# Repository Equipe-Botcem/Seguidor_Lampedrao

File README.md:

# Seguidor_Alpha

Código utilizado para controle e envio de comandos do robô seguidor de linha da equipe de competição BOTCEM UFSC.

## Índice

1. [Guia de Instalação e Execução](#Guia-de-Instalação-e-Execução)
2. [Pré-requisitos](#Pré-requisitos)
3. [Autoria e Contribuições](#Autoria-e-Contribuições)
4. [Fontes](#Fontes)
5. [Classes e Funções](#Classes-e-Funções)
    1. [Classe `Motor`](#Classe-Motor)
    2. [Classe `Driver`](#Classe-Driver)
    3. [Classe `Controlador`](#Classe-Controlador)
    4. [Classe `Seguidor`](#Classe-Seguidor)

## Guia de Instalação e Execução:

1. Extrair o arquivo zip.
2. Abrir a pasta `esp32_code` com a extensão PlatformIO do VScode.
3. Compilar o arquivo e transferi-lo para o ESP32.
4. Baixar o aplicativo Line-follower.apk.

## Pré-requisitos:

- Microcontrolador: esp32dev
- Sistema operacional: Linux 20.04
- IDE: Visual Studio Code
- Framework: Arduino

## Autoria e Contribuições:

Esse projeto é de autoria da equipe BOTCEM UFSC.

## Fontes:

Stack Overflow, c2022. Disponível em: <stackoverflow.com>. Acesso em: 18 de dezembro de 2022.

## Classes e Funções

Este projeto inclui várias classes e funções para controlar o robô. As classes incluem `Motor`, `Driver`, `Controlador` e `Seguidor`, cada uma responsável por um aspecto específico do controle do robô. As funções dentro dessas classes permitem controlar os motores, ler os sensores, calcular a saída do controlador PID, e mais.

Para obter uma descrição detalhada de cada classe e função, consulte a documentação do código-fonte. Aqui estão alguns destaques:

- `Motor`: Esta classe controla o motor de cada lado do robô.
- `Driver`: Esta classe controla os dois motores do robô.
- `Controlador`: Esta classe implementa um controlador PID (Proporcional, Integral, Derivativo).
- `Seguidor`: Esta classe é o principal controlador do robô seguidor de linha.

### Classe `Motor`

Essa classe controla o motor de cada lado do robô.

- `Motor(unsigned char PWM_1, unsigned char PWM_2, unsigned char EN, unsigned char OCM)`: Construtor da classe. Inicializa um motor com base nos pinos PWM, de habilitação (EN) e OCM.

- `void Init()`: Define os modos dos pinos como OUTPUT.

- `void Enable_drive()`: Habilita a unidade de motor acionando o pino EN.

- `void Disable_drive()`: Desabilita a unidade de motor e para o motor.

- `void Set_speed(int speed)`: Define a velocidade do motor. A velocidade pode ser positiva ou negativa, indicando a direção do motor.

### Classe `Driver`

Essa classe controla os dois motores do robô.

- `Driver(unsigned char *pins_dir, unsigned char *pins_esq)`: Construtor da classe. Inicializa os motores esquerdo e direito com base nos pinos fornecidos.

- `void Init()`: Inicializa os motores.

- `void setVB(int vb)`: Define a velocidade base dos motores.

- `void setMotors(int speed_esq, int speed_dir)`: Define a velocidade dos motores esquerdo e direito.

- `void Enable_motors_drives()`: Habilita os dois motores.

- `void Disable_motors_drives()`: Desabilita os dois motores.

- `void Break()`: Para os motores.

- `void Set_speedRot(int rot)`: Define a velocidade rotacional dos motores.

- `void teste()`: Uma função de teste que move os motores para frente e para trás.

### Classe `Controlador`

Essa classe implementa um controlador PID (Proporcional, Integral, Derivativo).

- `Controlador()`: Construtor da classe.

- `void setKp(float kp)`: Define o coeficiente proporcional do PID.

- `void setKd(float kd)`: Define o coeficiente derivativo do PID.

- `void setKi(float ki)`: Define o coeficiente integral do PID.

- `void setControlador(float kp, float kd, float ki)`: Define todos os coeficientes do PID.

- `float calcPID(float erro)`: Calcula a saída do PID com base no erro fornecido.

- `float getAmostragem()`: Retorna o tempo de amostragem do PID.

- `void resetConditions()`: Reseta as condições do PID.

- `void teste(float erro)`: Uma função de teste que imprime a saída do PID.

### Classe `Seguidor`

Essa classe é o principal controlador do robô seguidor de linha.

- `Seguidor()`: Construtor da classe.

- `void Config_...()`: Um conjunto de funções que configuram os pinos, sensores e motores do robô.

- `void initBluetooth()`: Inicializa a conexão Bluetooth.

- `void Init()`: Inicializa todos os componentes do robô.

- `void set_handler()`: Manipula os comandos recebidos pelo Bluetooth.

- `void calibration()`: Calibra os sensores de linha.

- `void controle()`: Controla os motores com base nos sensores de linha.

- `bool IsOut()`: Verifica se o robô está fora da linha.

- `void mapeamento()`: Mapeia o caminho do robô.

- `void Run()`: Inicia o robô.

- `void Stop()`: Para o robô.

- `void Behavior()`: Controla o comportamento do robô com base nos comandos recebidos pelo Bluetooth.

- `void comunica_serial()`: Lê comandos do Bluetooth.

- `void stopRoutine()`: Rotina para parar o robô.

- `bool CheckLateralDir()`, `bool CheckLateralEsq()`: Verifica se o robô chegou a um cruzamento à direita ou à esquerda.

- `bool isStart()`: Verifica se o robô está em movimento.

- `void bateryCheck()`: Verifica o nível da bateria.

- `void CheckLed()`, `void LigaLed()`, `void DesligaLed()`, `void PiscaLed(int num_piscadas)`: Funções para controlar os LEDs do robô.

- `void teste()`, `void TesteSensoresLat()`: Funções de teste para o robô.

### Diagrama de classes

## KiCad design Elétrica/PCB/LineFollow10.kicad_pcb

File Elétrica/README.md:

# Documentação do Projeto Eletrônico do Seguidor de Linha Alpha

## 1. Projeto Elétrico

O projeto elétrico tem seu funcionamento separado em três parte: potência (alimentação) e controle.

### 1.1. Potência

O circuito de potência é composto pelos seguintes elementos:

- Bateria: LiPo 7,4V 2S 300mAh;
- Conversor de tensão Step Up: XL6009;
- Regulador de Tensão 5V: LM7805;
- Regulador de Tensão 3.3V: LM1117;
- Capacitores de Filtro: 0.22uF, 0.1uF e 10uF.
- Diodo;
- Switchs.

### 1.2. Controle

O circuito de controle é composto pelos seguintes elementos:

- Shield ESP32;
- Drivers IC: TB9051FTG Single Brushed;
- Encoders;
- Sensores de Refletância: QRE1117;
- Resistores: 47Kohns e 47ohns.

## 2. Projeto da PCB

O projeto da PCB foi desenvolvido no software KiCAD.
As dimensões da placa são: 119mm X 151mm X 1.6mm (Comprimento X Largura X Altura).
A placa é composta por duas camadas de trilhas, inferior e superior.

## 3. Medições

### 3.1. Corrente Consumida

Realizando a medição do Seguidor de Linha por uma fonte de tensão, pode-se obter as seguintes medidas de consumo:

- Ligado: 300mA;
- Velocidade Baixa: 600mA;
- Velocidade Alta: 1.5A. 

## 4. Melhorias

- Desenvolvimento de uma placa totalmente integrada.

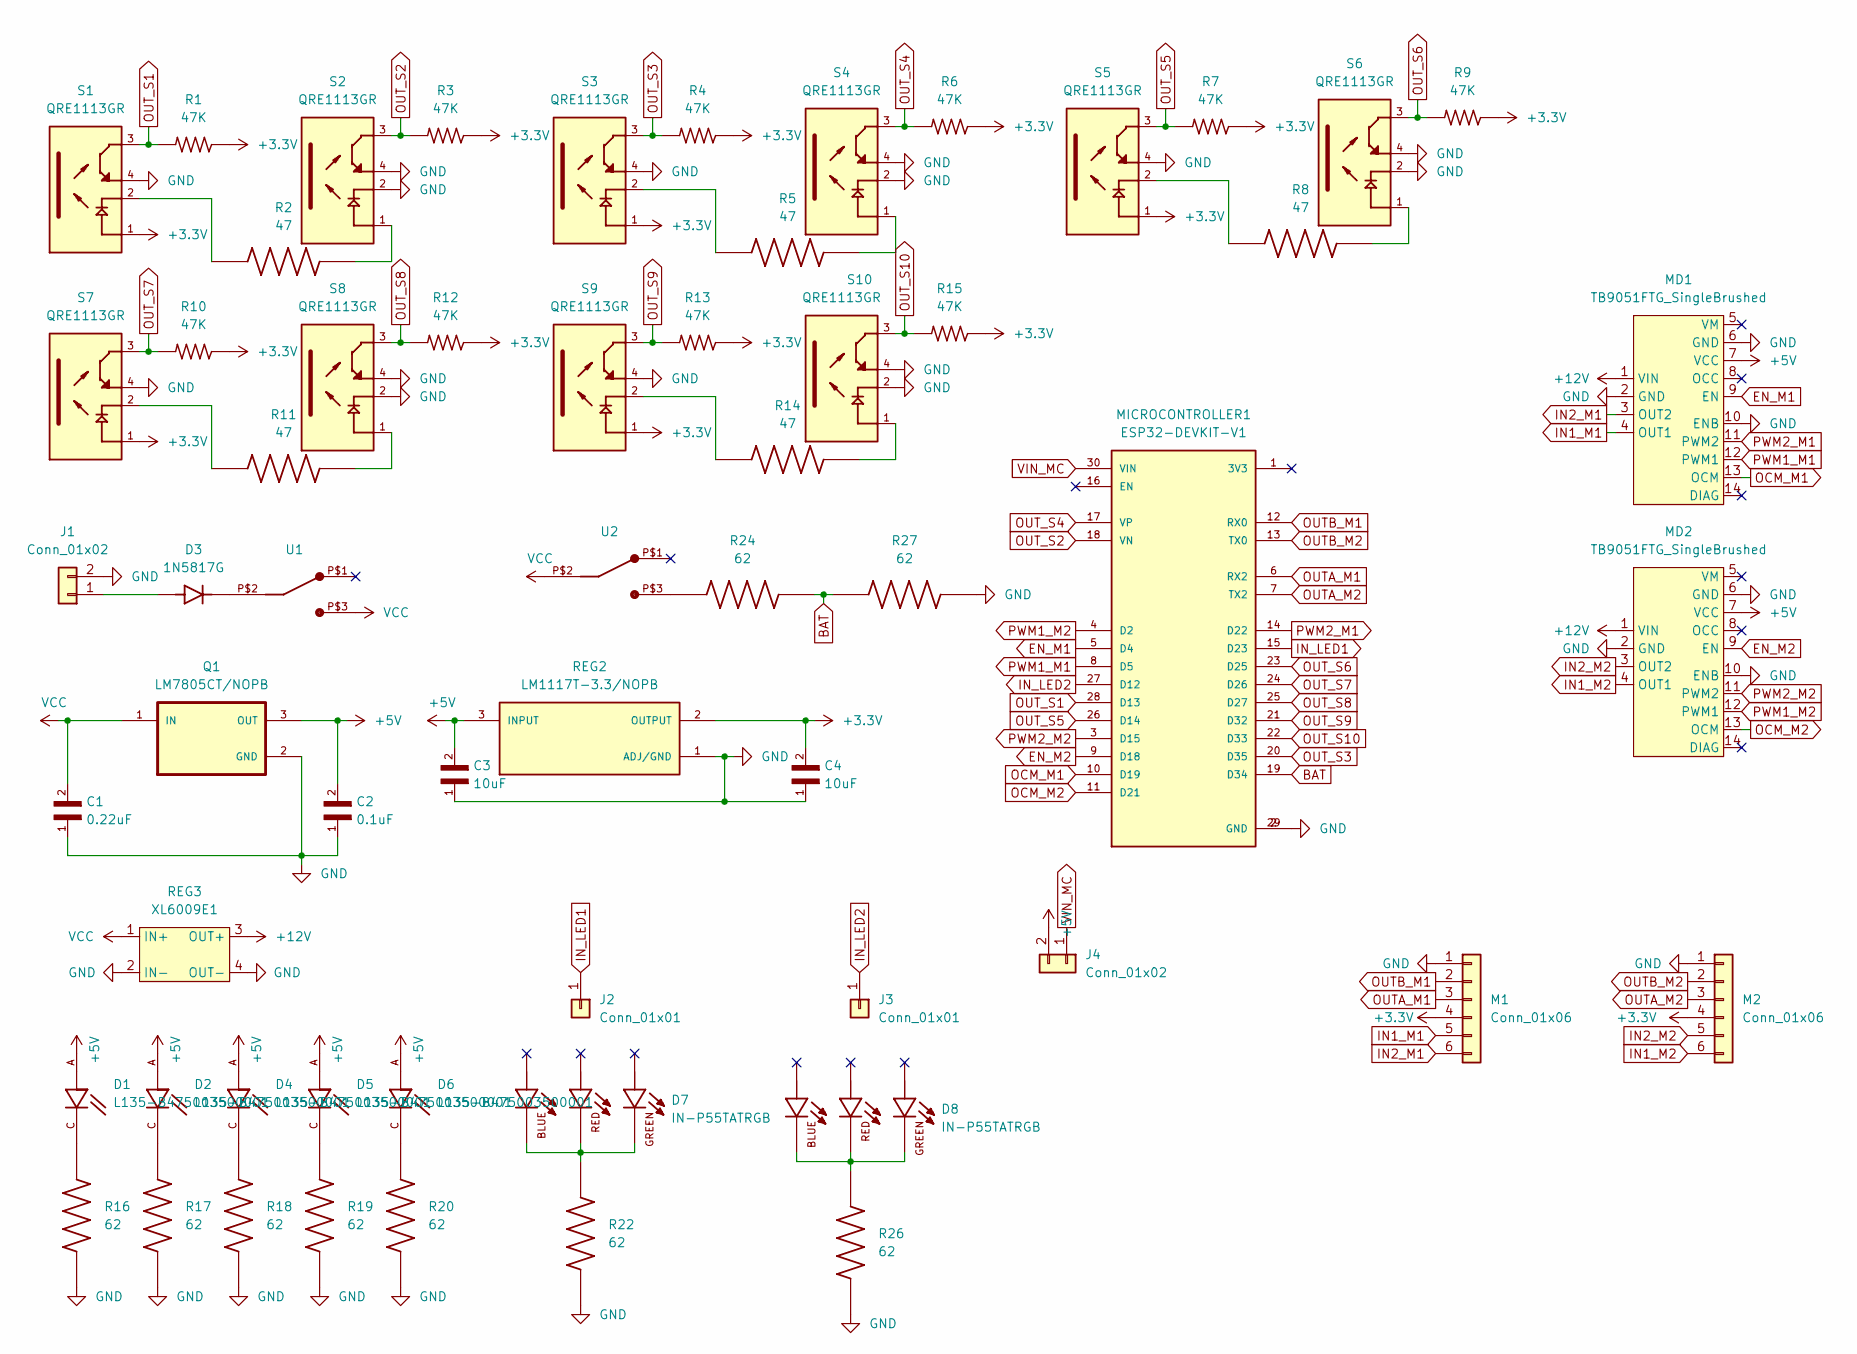
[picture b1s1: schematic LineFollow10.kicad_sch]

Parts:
C1: 0.22uF; CAPRB250W50L550T350H600; PARTREV 20200318
C2: 0.1uF; CAPRB500W50L450T300H550; PARTREV 20200310
C3, C4: 10uF; CAPRB500W50L450T300H550; PARTREV 20200310
D1, D2, D4, D5, D6: L135-B475003500001; LED_L135-B475003500001
D3: 1N5817G; DIOAD1036W78L470D235; PARTREV P2104
D7, D8: IN-P55TATRGB; LED_IN-P55TATRGB; PARTREV 1.0
J1: Conn_01x02; PinSocket_1x02_P2.54mm_Vertical
J2: Conn_01x01; SolderWire-0.1sqmm_1x01_D0.4mm_OD1mm
J3: Conn_01x01
J4: Conn_01x02
M1, M2: Conn_01x06; PinSocket_1x06_P2.54mm_Vertical
MD1, MD2: TB9051FTG_SingleBrushed
MICROCONTROLLER1: ESP32-DEVKIT-V1; MODULE_ESP32_DEVKIT_V1; PARTREV N/A
Q1: LM7805CT/NOPB; TO254P1054X470X2600-3; PARTREV LTR
R1, R3, R4, R6, R7, R9, R10, R12, R13, R15: 47K; RESAD640W45L370D200
R2, R5, R8, R11, R14: 47; RESAD716W44L360D186; PARTREV 11/16/2017
R16, R17, R18, R19, R20, R22, R24, R26, R27: 62; RESAD1100W55L680D260; PARTREV 201304
REG2: LM1117T-3.3/NOPB; TO254P1054X470X1955-3; PARTREV O
REG3: XL6009E1
S1, S2, S3, S4, S5, S6, S7, S8, S9, S10: QRE1113GR; SOIC180P460X187-4N; PARTREV 5
U1, U2: 0S102011MS2QN1

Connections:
+3.3V: C4.2, M1.4, M2.4, R1.1, R3.1, R4.1, R6.1, R7.1, R9.1, R10.1, R12.1, R13.1, R15.1, REG2.2 (OUTPUT), S1.1, S3.1, S5.1, S7.1, S9.1
+5V: C2.2, C3.2, D1.A, D2.A, D4.A, D5.A, D6.A, J4.2, MD1.7 (VCC), MD2.7 (VCC), Q1.3 (OUT), REG2.3 (INPUT)
+12V: MD1.1 (VIN), MD2.1 (VIN), REG3.3 (OUT+)
BAT: MICROCONTROLLER1.19 (D34), R24.1, R27.2
EN_M1: MD1.9 (EN), MICROCONTROLLER1.5 (D4)
EN_M2: MD2.9 (EN), MICROCONTROLLER1.9 (D18)
GND: C1.1, C2.1, C3.1, C4.1, J1.2, M1.1, M2.1, MD1.2 (GND), MD1.6 (GND), MD1.10 (ENB), MD2.2 (GND), MD2.6 (GND), MD2.10 (ENB), MICROCONTROLLER1.2 (GND), MICROCONTROLLER1.29 (GND), Q1.2 (GND), R16.1, R17.1, R18.1, R19.1, R20.1, R22.1, R26.1, R27.1, REG2.1 (ADJ/GND), REG3.2 (IN-), REG3.4 (OUT-), S1.4, S2.2, S2.4, S3.4, S4.2, S4.4, S5.4, S6.2, S6.4, S7.4, S8.2, S8.4, S9.4, S10.2, S10.4
IN1_M1: M1.5, MD1.4 (OUT1)
IN1_M2: M2.6, MD2.4 (OUT1)
IN2_M1: M1.6, MD1.3 (OUT2)
IN2_M2: M2.5, MD2.3 (OUT2)
IN_LED1: J2.1, MICROCONTROLLER1.15 (D23)
IN_LED2: J3.1, MICROCONTROLLER1.27 (D12)
unnamed: D1.C, R16.2
unnamed: D2.C, R17.2
unnamed: D3.A, J1.1
unnamed: D3.C, U1.P$2
unnamed: D4.C, R18.2
unnamed: D5.C, R19.2
unnamed: D6.C, R20.2
unnamed: D7.1, D7.2, D7.3, R22.2
unnamed: D8.1, D8.2, D8.3, R26.2
unnamed: R2.1, S1.2
unnamed: R2.2, S2.1
unnamed: R5.1, S3.2
unnamed: R5.2, S4.1
unnamed: R8.1, S5.2
unnamed: R8.2, S6.1
unnamed: R11.1, S7.2
unnamed: R11.2, S8.1
unnamed: R14.1, S9.2
unnamed: R14.2, S10.1
unnamed: R24.2, U2.P$3
OCM_M1: MD1.13 (OCM), MICROCONTROLLER1.10 (D19)
OCM_M2: MD2.13 (OCM), MICROCONTROLLER1.11 (D21)
OUTA_M1: M1.3, MICROCONTROLLER1.6 (RX2)
OUTA_M2: M2.3, MICROCONTROLLER1.7 (TX2)
OUTB_M1: M1.2, MICROCONTROLLER1.12 (RX0)
OUTB_M2: M2.2, MICROCONTROLLER1.13 (TX0)
OUT_S1: MICROCONTROLLER1.28 (D13), R1.2, S1.3
OUT_S2: MICROCONTROLLER1.18 (VN), R3.2, S2.3
OUT_S3: MICROCONTROLLER1.20 (D35), R4.2, S3.3
OUT_S4: MICROCONTROLLER1.17 (VP), R6.2, S4.3
OUT_S5: MICROCONTROLLER1.26 (D14), R7.2, S5.3
OUT_S6: MICROCONTROLLER1.23 (D25), R9.2, S6.3
OUT_S7: MICROCONTROLLER1.24 (D26), R10.2, S7.3
OUT_S8: MICROCONTROLLER1.25 (D27), R12.2, S8.3
OUT_S9: MICROCONTROLLER1.21 (D32), R13.2, S9.3
OUT_S10: MICROCONTROLLER1.22 (D33), R15.2, S10.3
PWM1_M1: MD1.12 (PWM1), MICROCONTROLLER1.8 (D5)
PWM1_M2: MD2.12 (PWM1), MICROCONTROLLER1.4 (D2)
PWM2_M1: MD1.11 (PWM2), MICROCONTROLLER1.14 (D22)
PWM2_M2: MD2.11 (PWM2), MICROCONTROLLER1.3 (D15)
VCC: C1.2, Q1.1 (IN), REG3.1 (IN+), U1.P$3, U2.P$2
VIN_MC: J4.1, MICROCONTROLLER1.30 (VIN)

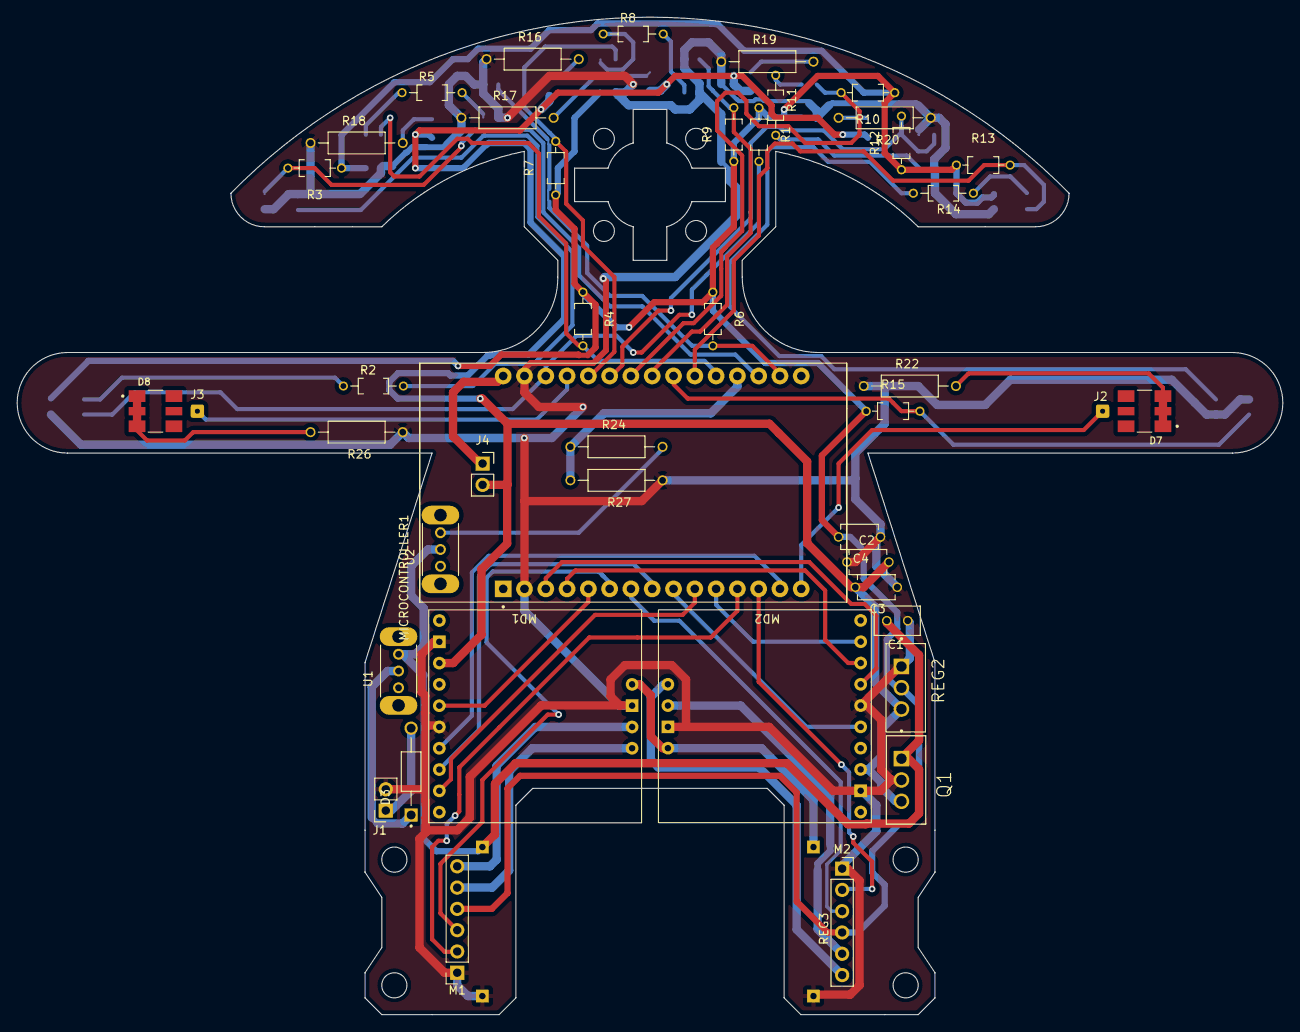
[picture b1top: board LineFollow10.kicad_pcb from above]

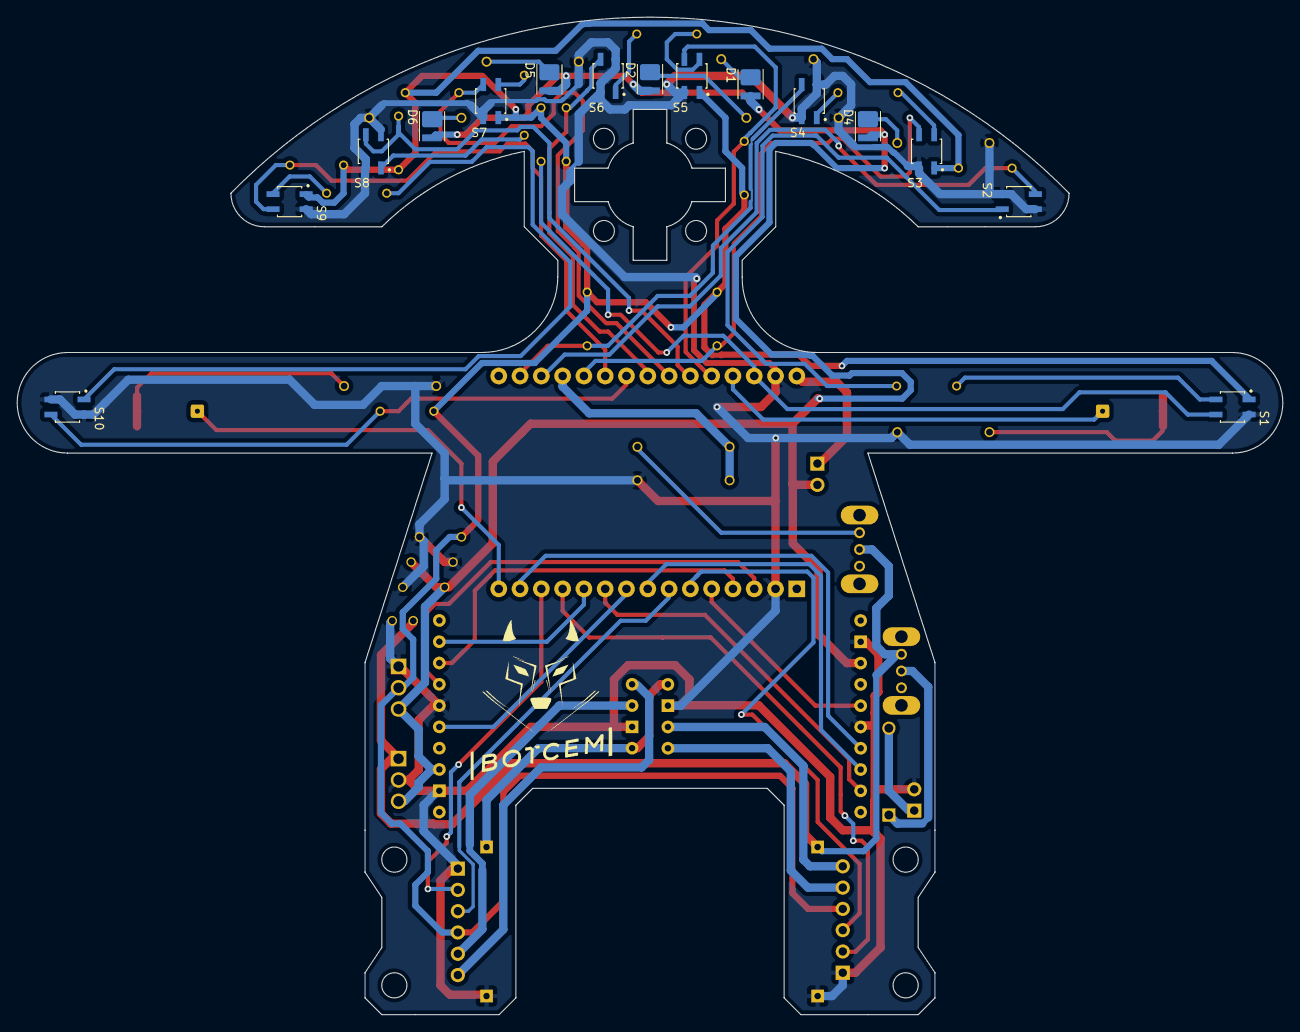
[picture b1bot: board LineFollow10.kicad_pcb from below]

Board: 2 copper layers, 151.0 x 119.0 mm, 64 parts (16 on the bottom side), 55 nets.

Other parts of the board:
G: LOGO; BOTCEMLOGO
REF: MountingHole_3mm
REF#2: MountingHole_2.5mm
REF#3: MountingHole_3mm

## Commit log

2022-08-08 upload codigo calibração modificado
2022-08-09 upload from vscode
2022-08-17 Adição da classe Motor_drive
2022-08-17 Adição do diagrama de classes
2022-08-22 reestruturação para organização em classes
2022-08-23 implementação dos códigos de teste
2022-08-29 atualização das classes e códigos dos testes
2022-09-02 ajustes nos parametros de teste
2022-09-11 teste dos encoders concluidos
2022-09-11 Correção estrutural das libs/includes
2022-09-12 Inicio da classe Seguidor
2022-09-12 código para o teste dos sensores
2022-11-05 Atualizado arquivo ini para o esp32
2022-11-05 Setup inicial do código
2022-11-05 Adição de um include com funções utilitárias
2022-11-05 Adição dos números dos pinos do esp32
2022-11-05 Refatorada classe do sensor para calibracao
2022-11-05 Refatorado função disable
2022-11-05 Adição do comportamento de histerese
2022-11-06 Tirado pino DIAG
2022-11-06 Refactor - Construtores sensores
2022-11-06 Adicionada biblioteca WIFI
2022-11-06 Adicionada funções Wifi
2022-11-06 Refactor - Sensor.h
2022-11-06 Refactor - Seguidor.h
2022-11-06 Comportamento da função main
2022-11-06 Refactor Seguidor.h
2022-11-06 Adicionado comportamento dos controladores
2022-11-06 Bugs correction
2022-11-06 Refactor Read_line
2022-11-06 Refactor Sensor_dir
2022-11-07 Sets parâmetros atualizados
2022-11-07 Refactor seguidor
2022-11-07 Refactor no código
2022-11-07 Alterando valor de retorno das funções de leitura
2022-11-08 Teste rearanjando pastas
2022-11-08 Retirado Controlador
2022-11-08 Teste sensor
2022-11-09 Funções de teste
2022-11-09 Retirado classe S Sensor_linha
2022-11-09 Tirado Utilities
2022-11-10 Leirura do sensores ajusda
2022-11-10 Pinos do motor ajustado
2022-11-10 Ajustada resolução de leitura
2022-11-10 Debug
2022-11-10 Ajustado behavior e controladores
2022-11-10 Método Setup
2022-11-10 Behavior e teste ajustado para set
2022-11-10 Setup bluetooth check
2022-11-10 Setup do VB
2022-11-10 Ajustes nos testes do setup
2022-11-10 Stop condition implemented
2022-11-10 Atraso do controlador retirado
2022-11-10 Ajustada Vmin pelo aplicativo
2022-11-10 Set_handler ajustado para Vmin
2022-11-10 Teste do processamento
2022-11-10 Refactor
2022-11-10 Ajustado tempo de processamento
2022-11-12 Funcionando
2022-11-13 Cödigo funcional
2022-11-14 Código funcional
2022-11-14 Código com negativa
2022-11-16 Côdigo final
2023-01-25 Deletando código antigo
    Deletando código usado na competição do instituto Mauá
2023-01-25 Atualizando nomes de pastas
2023-01-25 Atualizando diretórios
2023-01-31 codigo com telemetria parcial
2023-03-24 Callibração refatorada
2023-03-24 Add validação telemetria
2023-03-25 Refactor calibalibration
2023-03-25 Calibração corrigida
2023-03-25 Refactor code
2023-03-26 Fix bugs calibration
2023-03-30 Add testes
2023-03-30 Add controlador
2023-03-30 Add D e I
2023-04-05 Teste classe controlador
2023-04-18 Add pinos
2023-04-18 Add config leds
2023-04-18 Remove test operation
2023-04-19 Add teste motor
2023-04-19 Add calibration values
2023-04-20 Invert pinos motor 1
2023-04-20 Add KI handler
2023-04-21 Versäo final
2023-04-21 Dividido por 10000
2023-04-21 Add parada quando perder a linha
2023-04-21 Add changes to main
2023-04-21 Add pedros functions
2023-04-22 Code partialy working
2023-04-22 Code working
2023-05-11 Fix controlador
2023-05-11 Hotfix
2023-05-11 Adicionando os arquivos do projeto da PCB
2023-05-12 Adicionando os componentes do projeto
2023-05-12 Adicionando os arquivos do SolidWorks da estrutura
2023-05-18 Add leitura com angulo
2023-05-23 Refactor get angle
2023-05-24 Refactor angle
2023-05-25 Update and rename ReadMe.md to README.md
    Adicionando documentação
2023-05-25 Update README.md
    Atualizando documentação
2023-05-25 Add getAngle
2023-05-25 Add kalman filter lib and control
2023-05-25 FIx lib
2023-05-25 Fix return to line
2023-05-31 Add kalman filter
2023-05-31 Revert "Sensor fusion"
2023-06-07 Kalman filter visualization
2023-06-07 Ajuste teste
2023-07-11 Remove Legacy
2023-07-11 Add CLass Sensor_linha
2023-07-11 Add teste sensores
2023-07-13 Add PID digital
2023-07-13 FIltro encapsulado
2023-07-16 Add Drive
2023-07-18 Add break
2023-07-19 bateria
2023-07-20 WIP: Teste parada
2023-07-21 Recebimento de parâmetros
2023-07-23 WIP: Implementado translacional
2023-07-23 Bug fix
2023-07-23 Add translacional
2023-07-23 Fix Cmin and ENCH calibration
2023-07-25 Add mapeamento
2023-07-26 Code competição
2023-07-29 Testes
2023-08-01 add comentarios main.cpp
2023-09-08 Add app mais novo
2023-09-08 Alterado nome do bluetooth
2023-09-08 Dim variacao
2023-09-10 Alteracoes competicao
2023-09-10 Consertado print
2024-03-02 changes_IR
2024-03-02 42segundos
    obteve 42 segundos aqui
2024-03-02 add serialBT para ver encoders
2024-03-02 adição de pinos_encoder(mudança de pinos pwm)
2024-03-03 encoder_funcional
    atribuição de lib do encoder com ele funcionando, falta logica para controle de motores por feedback dos encoders
2024-03-03 controler for encoder
